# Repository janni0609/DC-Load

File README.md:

# DC Electronic Load

A programmable DC electronic load built on the Raspberry Pi Pico 2 (RP2350). It sinks a user-defined current from a DC source under test and measures voltage, current, power, capacity, and energy in real time on a colour TFT display.

## Hardware

| Component | Part | Interface |
|---|---|---|
| MCU | Raspberry Pi Pico 2 (RP2350) | — |
| Display | ILI9488 TFT 240×320 | SPI (GPIO 16/18/19/17/20) |
| DAC (current setpoint) | DAC80501 16-bit | I2C1 0x48 |
| ADC (V + I measurement) | ADS1115 16-bit | I2C1 0x49 |
| I/O expander (buttons/encoder) | TCAL9539 16-bit | I2C1 0x74 |
| Temperature sensors | 3× MCP9700 | ADC (GPIO 26/27/28) |
| Fans | 2× PWM | GPIO 2, 3 (25 kHz) |
| Beeper | — | GPIO 22 |

I2C1 runs on GPIO 14 (SDA) / GPIO 15 (SCL) at 1 MHz.

### Board design

KiCad design files live in [`hardware/`](hardware/):

- [`hardware/PlugInDC Load/`](hardware/PlugInDC%20Load/) — main plug-in board (MCU, DAC/ADC, pass elements, power supply)
- [`hardware/Front Panel/`](hardware/Front%20Panel/) — front panel board

Each project includes the schematic, PCB layout, a schematic PDF, and a STEP model.

## Specifications

| Parameter | Range |
|---|---|
| Input voltage | 0 – 100 V |
| Set current | 0 – 100 A |
| Under-voltage / CV setpoint (UVP) | 0 – 99.99 V |
| Max power (beeper threshold) | 1000 W |

The DAC output (0–2.5 V) drives the current-control circuit: 2.5 V = 100 A full scale. The ADS1115 uses auto-ranging PGA for both channels, scaling 2.5 V → 100 V (voltage) and 2.5 V → 100 A (current).

## Display Layout

Portrait 240×320, divided into sections:

```
┌──────────────────────────┐
│    DC ELECTRONIC LOAD    │  ← green = load ON, yellow = load OFF
├──────────────────────────┤
│ VOLTAGE          xx.xx V │
├──────────────────────────┤
│ CURRENT         x.xxx A  │
├──────────────────────────┤
│ POWER           xxx.xx W │
├──────────────┬───────────┤
│ CAPACITY x.xxx Ah │ x.xx Wh ENERGY │
├──────────────┬───────────┤
│ SET CURR x.x A │ SET UVP xx.xx V │  ← UVP turns red in CV mode
├──────────────┬───────────┤
│ TEMP  xx.x°C │ HH:MM:SS  │
└──────────────┴───────────┘
```

## Controls

All buttons and the rotary encoder are read via the TCAL9539 I/O expander. Button behaviour is context-sensitive: the main screen, debug screen, and calibration screens each respond differently.

### Main screen

| Input | Function |
|---|---|
| Rotary encoder | Increment/decrement the selected digit of the active setpoint |
| P0.0 (encoder push) | Toggle between editing **SET CURR** and **SET UVP** |
| P0.3 | Move cursor left |
| P0.4 | Move cursor right |
| P0.5 | Switch to debug screen |
| P0.6 | Reset elapsed timer and clear Ah/Wh accumulators |
| P0.7 | Toggle internal / external voltage sense |
| P1.0 | Load ON / OFF (blocked while OTP is active) |

### Debug screen

The debug screen is a navigable menu. P0.3/P0.4 move the selection, the encoder adjusts the highlighted item, and P0.0 (encoder push) activates it.

| Menu item | Function |
|---|---|
| I SENSE | Toggle internal / external current shunt (persisted to EEPROM) |
| VOLT CAL | Enter voltage calibration wizard |
| CURR CAL | Enter current calibration wizard |
| VIEW CAL | Display stored calibration tables |
| OTP TRIP | Set over-temperature protection threshold with encoder (persisted) |
| UVP Kp | Adjust UVP PI proportional gain with encoder (persisted) |
| UVP Ki | Adjust UVP PI integral gain with encoder (persisted) |

### Calibration screen

| Input | Function |
|---|---|
| Rotary encoder | Adjust the entered reference value |
| P0.3 / P0.4 | Move digit cursor left / right |
| P0.0 (encoder push) | Confirm step and advance |
| P0.5 | Cancel and return to debug screen |

## UVP / Constant-Voltage Mode

When **SET UVP** is non-zero and the load is on, a software PI controller monitors the measured voltage. If it drops below the UVP setpoint, the controller reduces the sink current to regulate voltage at that level (constant-voltage / CV mode). The SET UVP field turns red while CV mode is active.

CV mode exits with 0.5 V hysteresis to avoid chattering. The PI gains (Kp, Ki) are tunable from the debug screen and stored in EEPROM.

## Over-Temperature Protection (OTP)

The OTP threshold (default 70 °C, adjustable 30–120 °C) is compared against the highest reading across all three MCP9700 sensors. When the threshold is exceeded:

- The load is turned off immediately.
- Five 500 ms beeps are sounded.
- The load ON button is blocked until the temperature drops 5 °C below the threshold.

## Fan Control

Fan speed is temperature-controlled using the highest reading across all three MCP9700 sensors:

- Off below 30 °C
- Linear ramp from 0–100 % between 30 °C and 50 °C
- Full speed above 50 °C

## Calibration

Both voltage and current channels support piecewise-linear calibration (4 points for voltage, 5 for current). The calibration wizard drives the load to each reference point, reads the raw ADC value, and prompts for the reference meter reading. Calibration data is stored in EEPROM and applied on every measurement via `piecewiseLerp`.

### EEPROM layout

| Address | Content |
|---|---|
| 0 | Current shunt select (0x01 = external) |
| 1 | Current cal valid marker (0xCA) |
| 2 | Voltage cal valid marker (0xCA) |
| 3–42 | Current cal: 5× raw + 5× user (10 floats) |
| 43–74 | Voltage cal: 4× raw + 4× user (8 floats) |
| 75 | OTP valid marker (0xCA) |
| 76–79 | OTP threshold (float) |
| 80 | UVP PI valid marker (0xCA) |
| 81–84 | UVP Kp (float) |
| 85–88 | UVP Ki (float) |

## Building

The project uses [PlatformIO](https://platformio.org/) with the Arduino framework.

```bash
# Build
pio run

# Upload
pio run --target upload

# Serial monitor
pio device monitor --baud 115200
```

Target board: `rpipico2`. Dependencies are fetched automatically (`Bodmer/TFT_eSPI`).

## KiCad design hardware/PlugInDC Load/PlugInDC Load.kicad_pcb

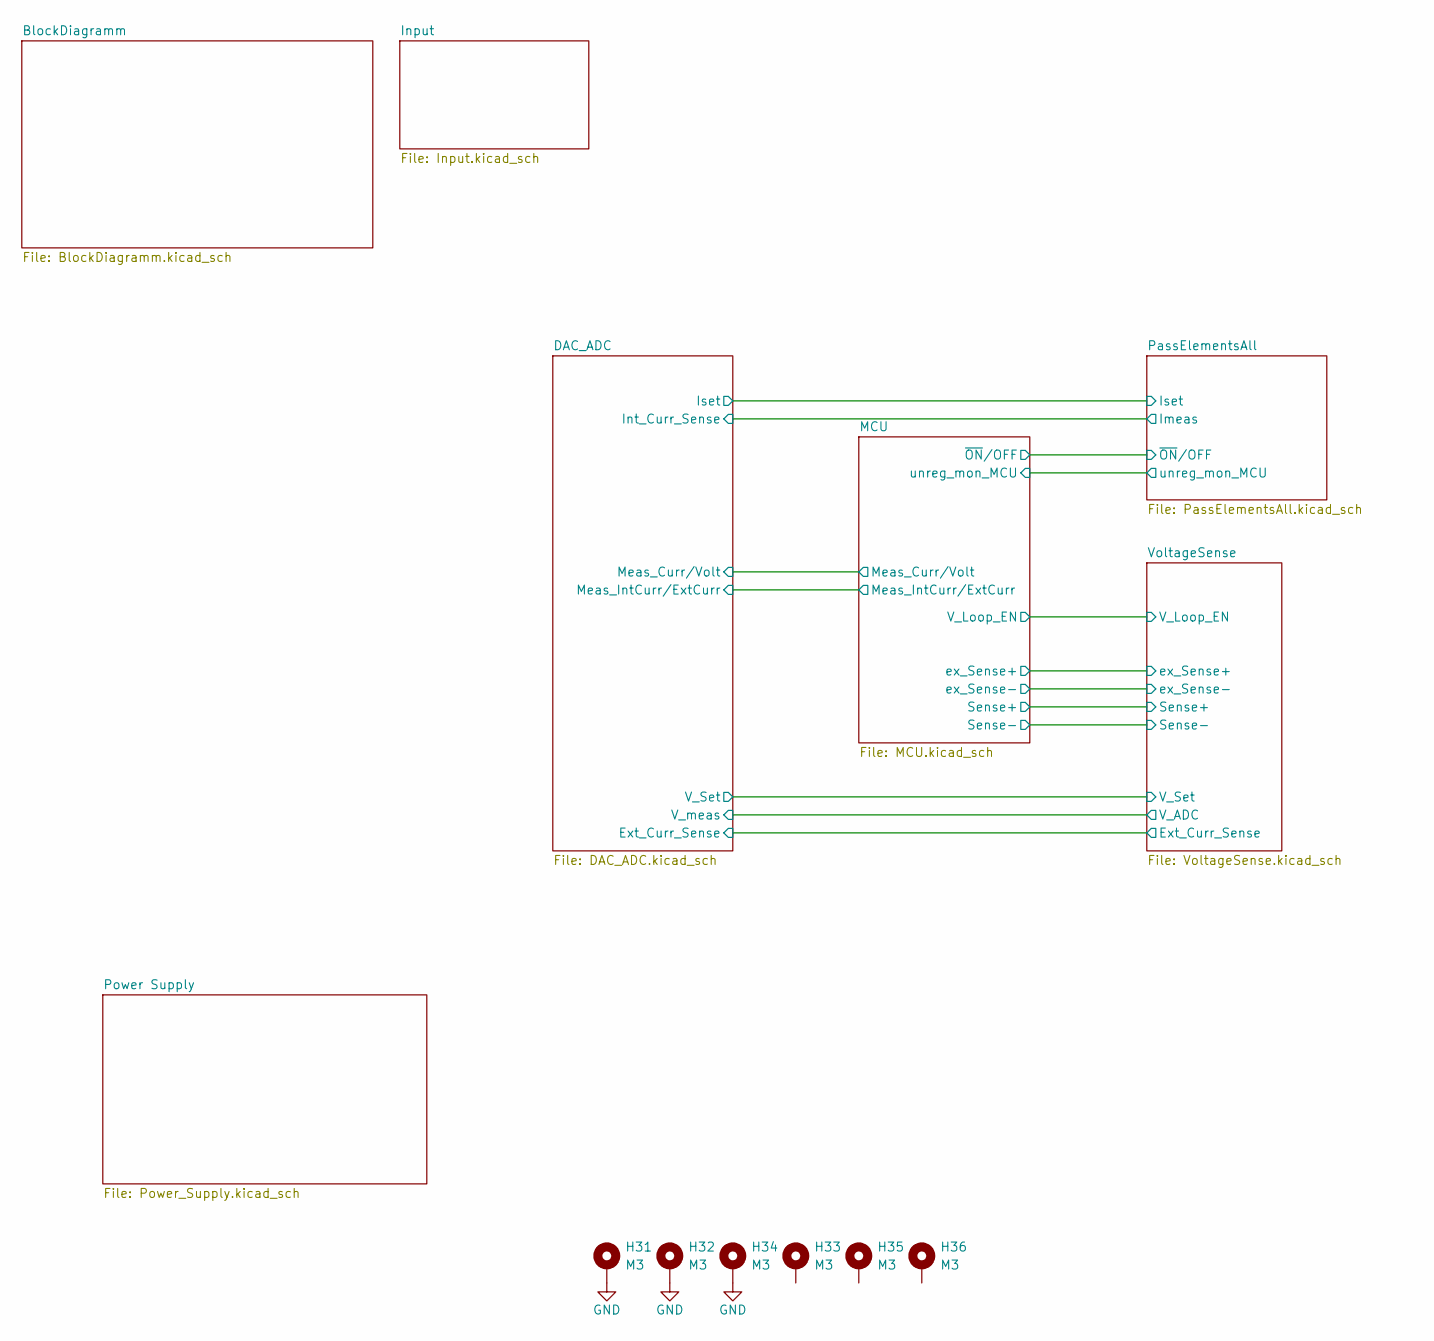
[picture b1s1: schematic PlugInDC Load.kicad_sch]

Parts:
H31, H32, H33, H34, H35, H36: M3; MountingHole_3.2mm_M3_DIN965_Pad

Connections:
GND: H31.1 (1_1), H32.1 (1_1), H34.1 (1_1); also elsewhere on the board

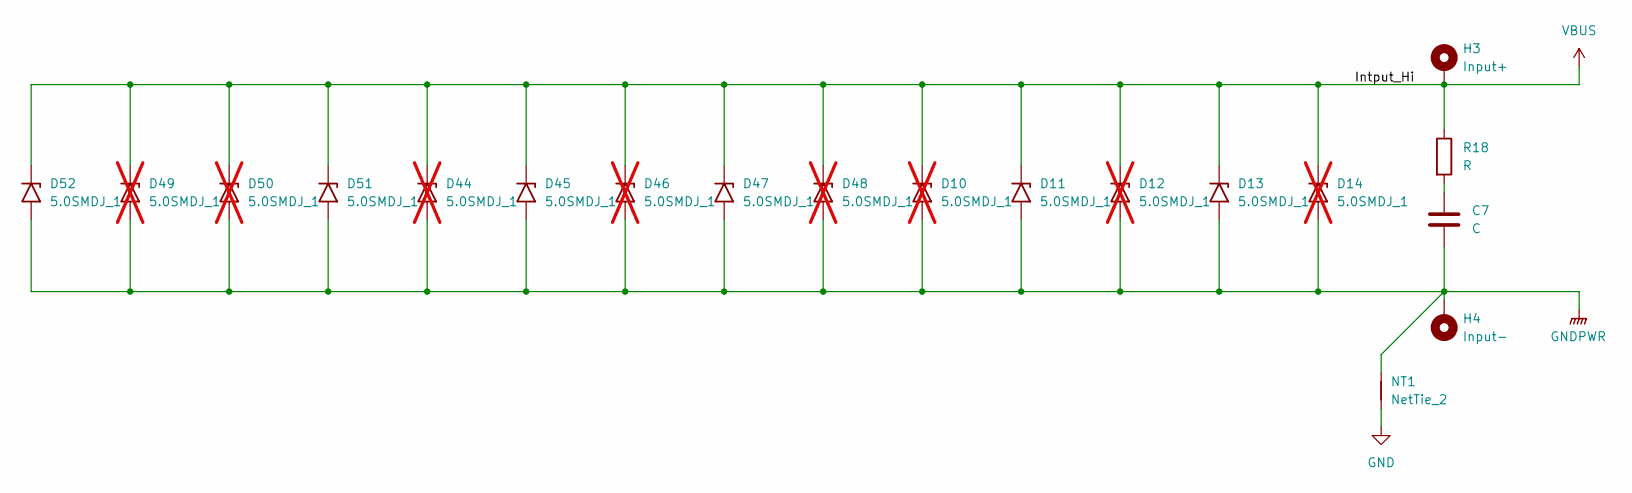
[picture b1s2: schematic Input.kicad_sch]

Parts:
C7: C; C_1206_3216Metric
D10, D12, D14, D44, D46, D48, D49, D50: 5.0SMDJ_1; D_SMC; not fitted
D11, D13, D45, D47, D51, D52: 5.0SMDJ_1; D_SMC
H3: Input+; MountingHole_4.3mm_M4_DIN965_Pad
H4: Input-; MountingHole_4.3mm_M4_DIN965_Pad
NT1: NetTie_2; NetTie-2_SMD_Pad2.0mm
R18: R; R_1206_3216Metric

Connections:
GND: NT1.1; also elsewhere on the board
GNDPWR: C7.2, D10.2 (A2), D11.2 (A2), D12.2 (A2), D13.2 (A2), D14.2 (A2), D44.2 (A2), D45.2 (A2), D46.2 (A2), D47.2 (A2), D48.2 (A2), D49.2 (A2), D50.2 (A2), D51.2 (A2), D52.2 (A2), H4.1 (1_1), NT1.2; also elsewhere on the board
unnamed: C7.1, R18.2
VBUS: D10.1 (A1), D11.1 (A1), D12.1 (A1), D13.1 (A1), D14.1 (A1), D44.1 (A1), D45.1 (A1), D46.1 (A1), D47.1 (A1), D48.1 (A1), D49.1 (A1), D50.1 (A1), D51.1 (A1), D52.1 (A1), H3.1 (1_1), R18.1; also elsewhere on the board

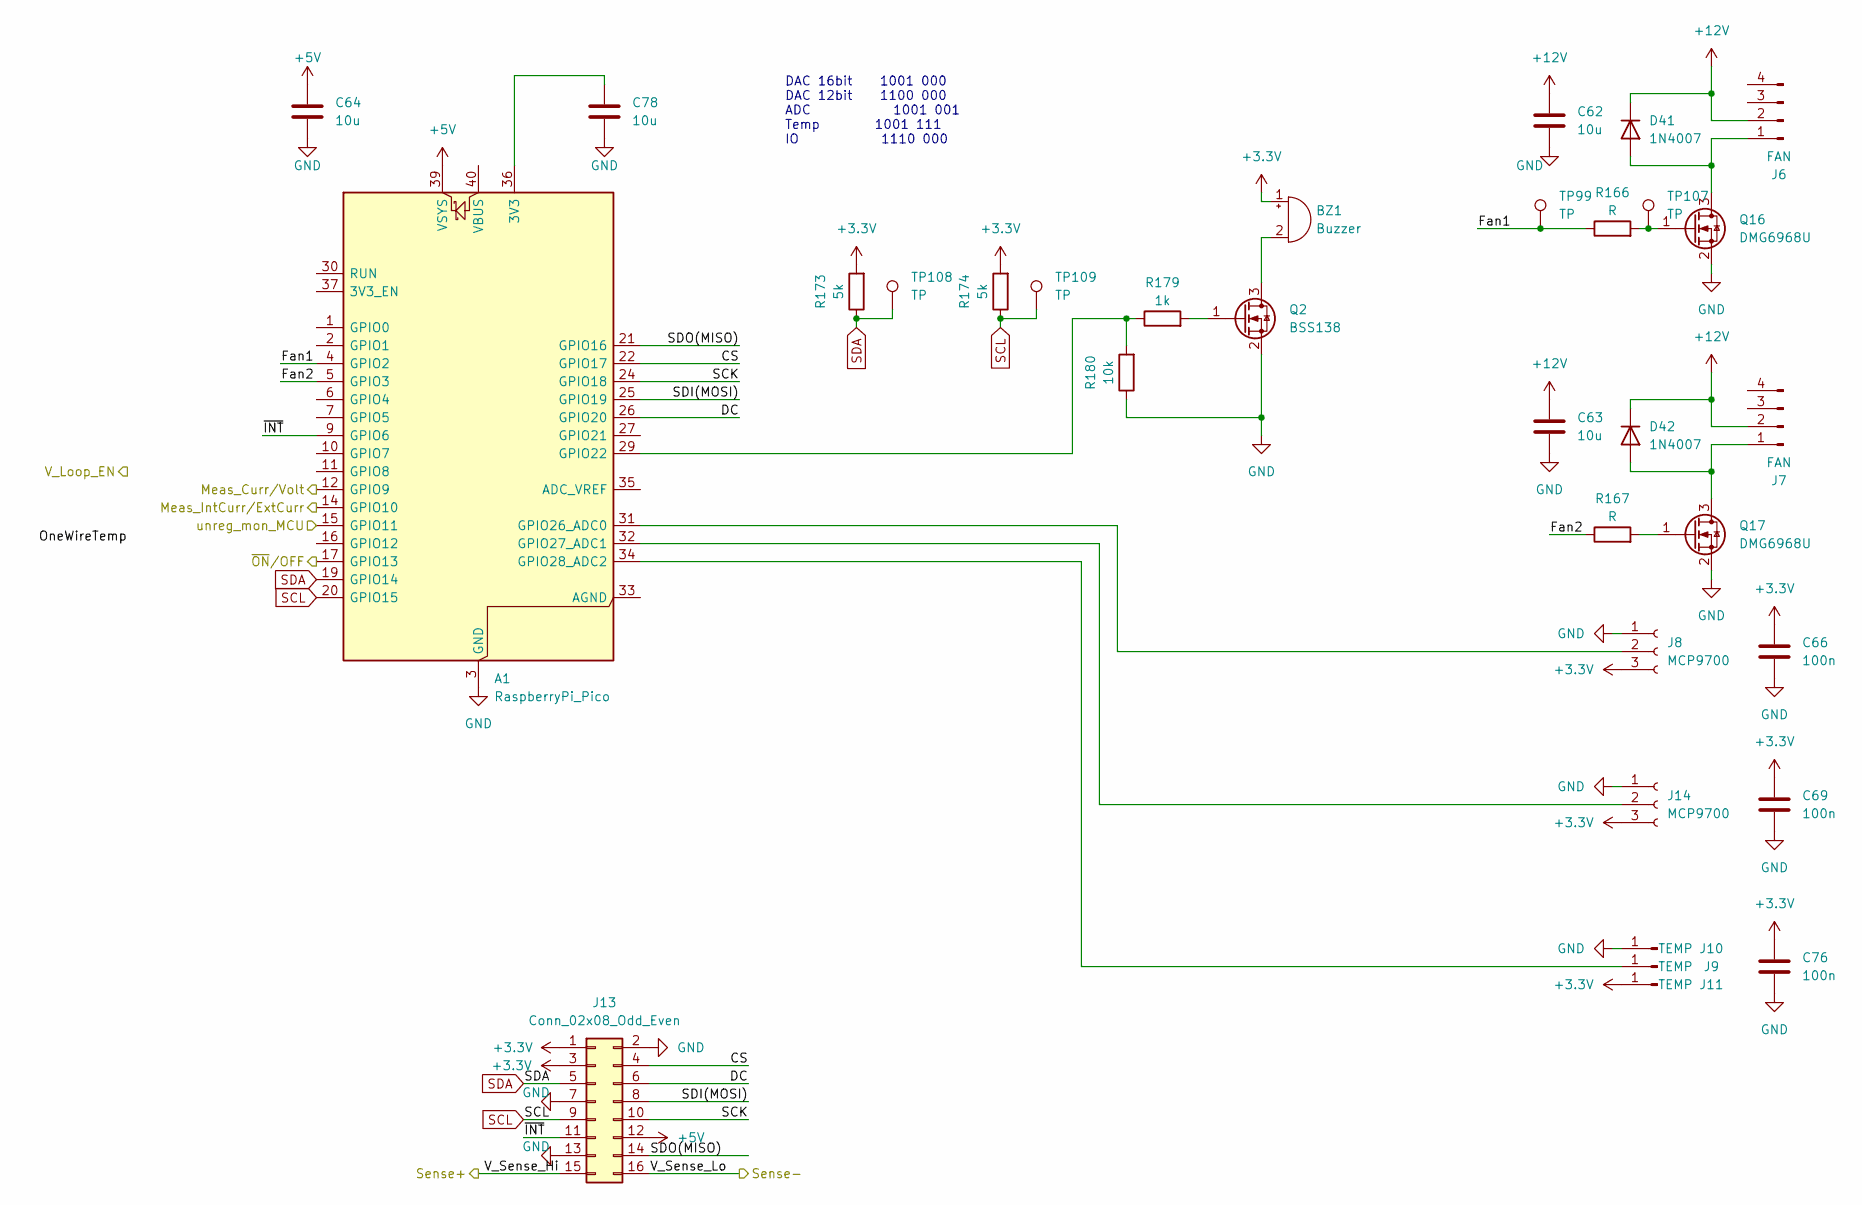
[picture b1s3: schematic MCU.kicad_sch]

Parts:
A1: RaspberryPi_Pico; RaspberryPi_Pico_Common_Unspecified
BZ1: Buzzer; Buzzer_12x9.5RM7.6
C62, C63: 10u; C_1206_3216Metric
C64, C78: 10u; C_0805_2012Metric
C66, C69, C76: 100n; C_0603_1608Metric
D41, D42: 1N4007; D_SOD-123F
J6, J7: FAN; FanPinHeader_1x04_P2.54mm_Vertical
J8, J14: MCP9700; JST_XH_B3B-XH-A_1x03_P2.50mm_Vertical
J9, J10, J11: TEMP; SolderWirePad_1x01_SMD_1.5x3mm
J13: Conn_02x08_Odd_Even; IDC-Header_2x08_P2.54mm_Vertical
Q2: BSS138; SOT-23-3
Q16, Q17: DMG6968U; SOT-23-3
R166, R167: R; R_0603_1608Metric
R173, R174: 5k; R_0603_1608Metric
R179: 1k; R_0603_1608Metric
R180: 10k; R_0603_1608Metric
TP99, TP107, TP108, TP109: TP; TestPoint_Pad_D1.0mm

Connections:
+3.3V: BZ1.1 (+), C66.1, C69.1, C76.1, J8.3, J11.1 (Pin_1_1), J13.1, J13.3, J14.3, R173.2, R174.2; also elsewhere on the board
+5V: A1.39 (VSYS), C64.1, J13.12; also elsewhere on the board
+12V: C62.1, C63.1, D41.1 (K), D42.1 (K), J6.2, J7.2; also elsewhere on the board
/DAC_ADC/Meas_IntCurr/ExtCurr: A1.14 (GPIO10); also elsewhere on the board
/MCU/CS: A1.22 (GPIO17), J13.4
/MCU/DC: A1.26 (GPIO20), J13.6
/MCU/Fan1: A1.4 (GPIO2), R166.1, TP99.1 (1_1)
/MCU/Fan2: A1.5 (GPIO3), R167.1
/MCU/Meas_Curr/Volt: A1.12 (GPIO9)
/MCU/OneWireTemp: A1.16 (GPIO12)
/MCU/SCK: A1.24 (GPIO18), J13.10
/MCU/SDI(MOSI): A1.25 (GPIO19), J13.8
/MCU/SDO(MISO): A1.21 (GPIO16), J13.14
/MCU/V_Loop_EN: A1.11 (GPIO8)
/MCU/V_Sense_Hi: J13.15; also elsewhere on the board
/MCU/V_Sense_Lo: J13.16; also elsewhere on the board
/MCU/unreg_mon_MCU: A1.15 (GPIO11); also elsewhere on the board
/MCU/~INT: A1.9 (GPIO6), J13.11
/MCU/~ON/OFF: A1.17 (GPIO13); also elsewhere on the board
GND: A1.3 (GND), A1.8 (GND), A1.13 (GND), A1.18 (GND), A1.23 (GND), A1.28 (GND), A1.38 (GND), C62.2, C63.2, C64.2, C66.2, C69.2, C76.2, C78.2, J8.1, J10.1 (Pin_1_1), J13.2, J13.7, J13.13, J14.1, Q2.2 (S), Q16.2 (S), Q17.2 (S), R180.1; also elsewhere on the board
unnamed: A1.36 (3V3), C78.1
unnamed: A1.29 (GPIO22), R179.1, R180.2
unnamed: A1.31 (GPIO26_ADC0), J8.2
unnamed: A1.32 (GPIO27_ADC1), J14.2
unnamed: A1.34 (GPIO28_ADC2), J9.1 (Pin_1_1)
unnamed: BZ1.2 (-), Q2.3 (D)
unnamed: D41.2 (A), J6.1, Q16.3 (D)
unnamed: D42.2 (A), J7.1, Q17.3 (D)
unnamed: Q2.1 (G), R179.2
unnamed: Q16.1 (G), R166.2, TP107.1 (1_1)
unnamed: Q17.1 (G), R167.2
SCL: A1.20 (GPIO15), J13.9, R174.1, TP109.1 (1_1); also elsewhere on the board
SDA: A1.19 (GPIO14), J13.5, R173.1, TP108.1 (1_1); also elsewhere on the board

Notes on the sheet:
DAC 16bit 1001 000 DAC 12bit 1100 000 ADC 1001 001 Temp 1001 111 IO 1110 000

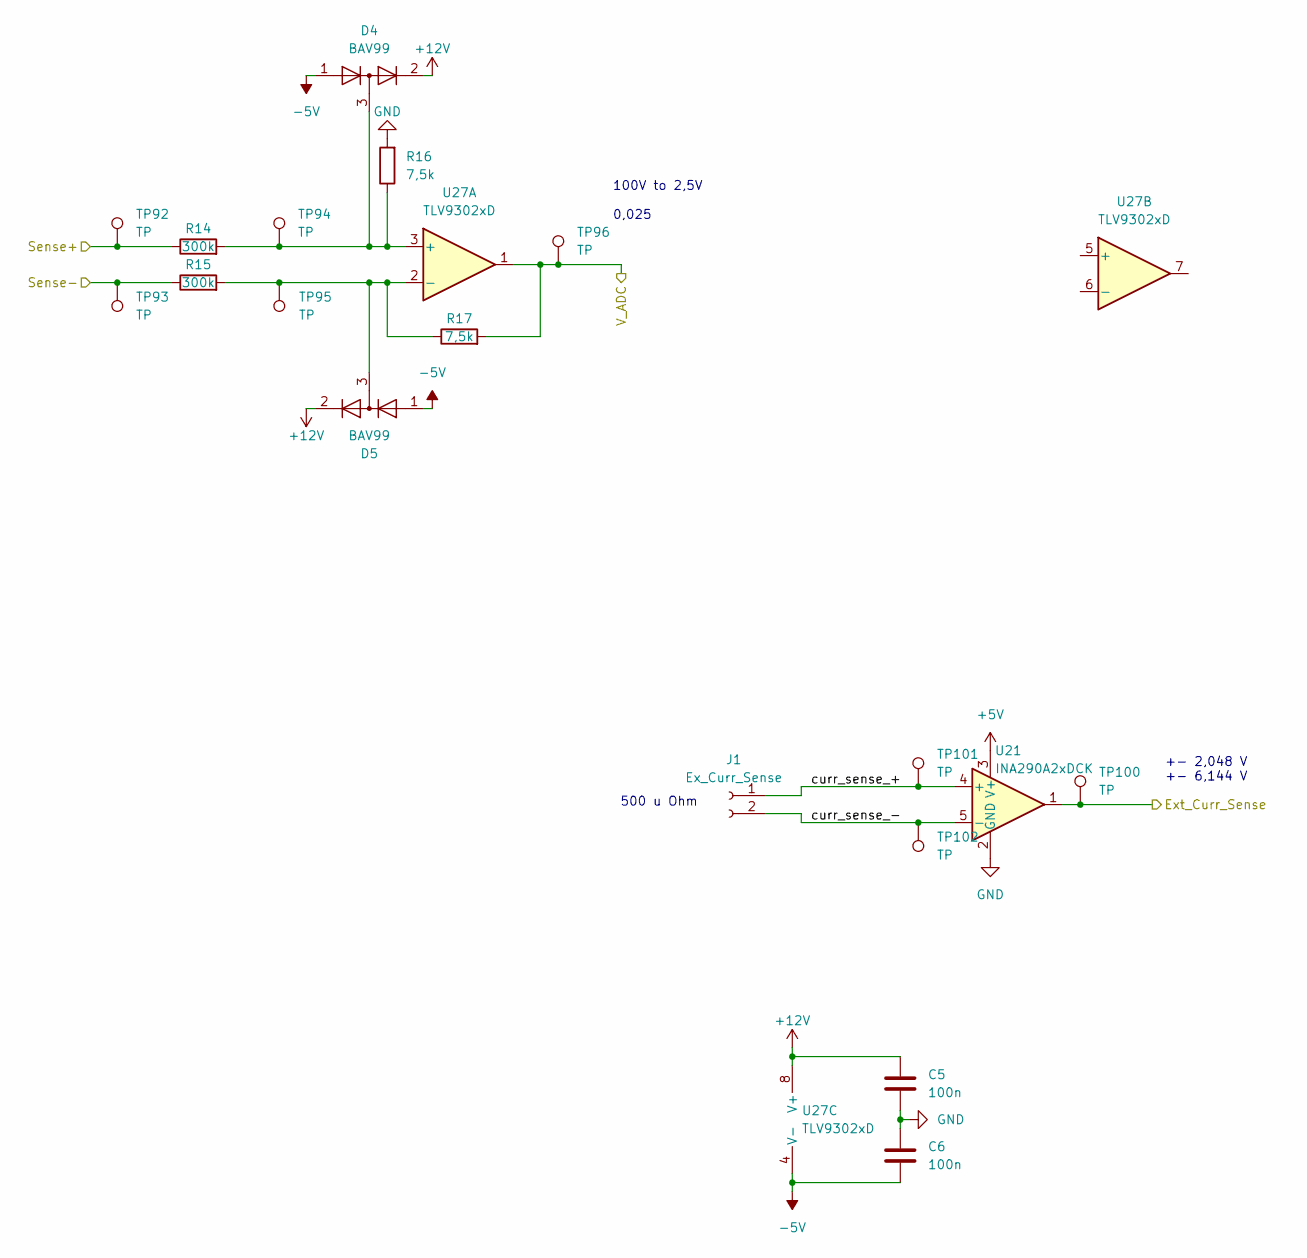
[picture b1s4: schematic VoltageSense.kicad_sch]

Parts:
C5, C6: 100n; C_0603_1608Metric
D4, D5: BAV99; SOT-23-3
J1: Ex_Curr_Sense; JST_XH_B2B-XH-A_1x02_P2.50mm_Vertical
R14, R15: 300k; R_0805_2012Metric
R16, R17: 7,5k; R_0805_2012Metric
TP92, TP93, TP94, TP95, TP96, TP100, TP101, TP102: TP; TestPoint_Pad_D1.0mm
U21: INA290A2xDCK; SOT-353_SC-70-5
U27: TLV9302xD; SOIC-8_3.9x4.9mm_P1.27mm

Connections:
+5V: U21.3 (V+); also elsewhere on the board
+12V: C5.1, D4.2 (A), D5.2 (A), U27.8 (V+); also elsewhere on the board
-5V: C6.2, D4.1 (K), D5.1 (K), U27.4 (V-); also elsewhere on the board
/DAC_ADC/Ext_Curr_Sense: TP100.1 (1_1), U21.1; also elsewhere on the board
/DAC_ADC/V_meas: R17.2, TP96.1 (1_1), U27.1; also elsewhere on the board
/MCU/V_Sense_Hi: R14.1, TP92.1 (1_1); also elsewhere on the board
/MCU/V_Sense_Lo: R15.1, TP93.1 (1_1); also elsewhere on the board
/VoltageSense/curr_sense_+: J1.1, TP101.1 (1_1), U21.4 (+)
/VoltageSense/curr_sense_-: J1.2, TP102.1 (1_1), U21.5 (-)
GND: C5.2, C6.1, R16.2, U21.2 (GND); also elsewhere on the board
unnamed: D4.3 (K), R14.2, R16.1, TP94.1 (1_1), U27.3 (+)
unnamed: D5.3 (K), R15.2, R17.1, TP95.1 (1_1), U27.2 (-)

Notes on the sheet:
500 u Ohm
100V to 2,5V 0,025
+- 2,048 V +- 6,144 V

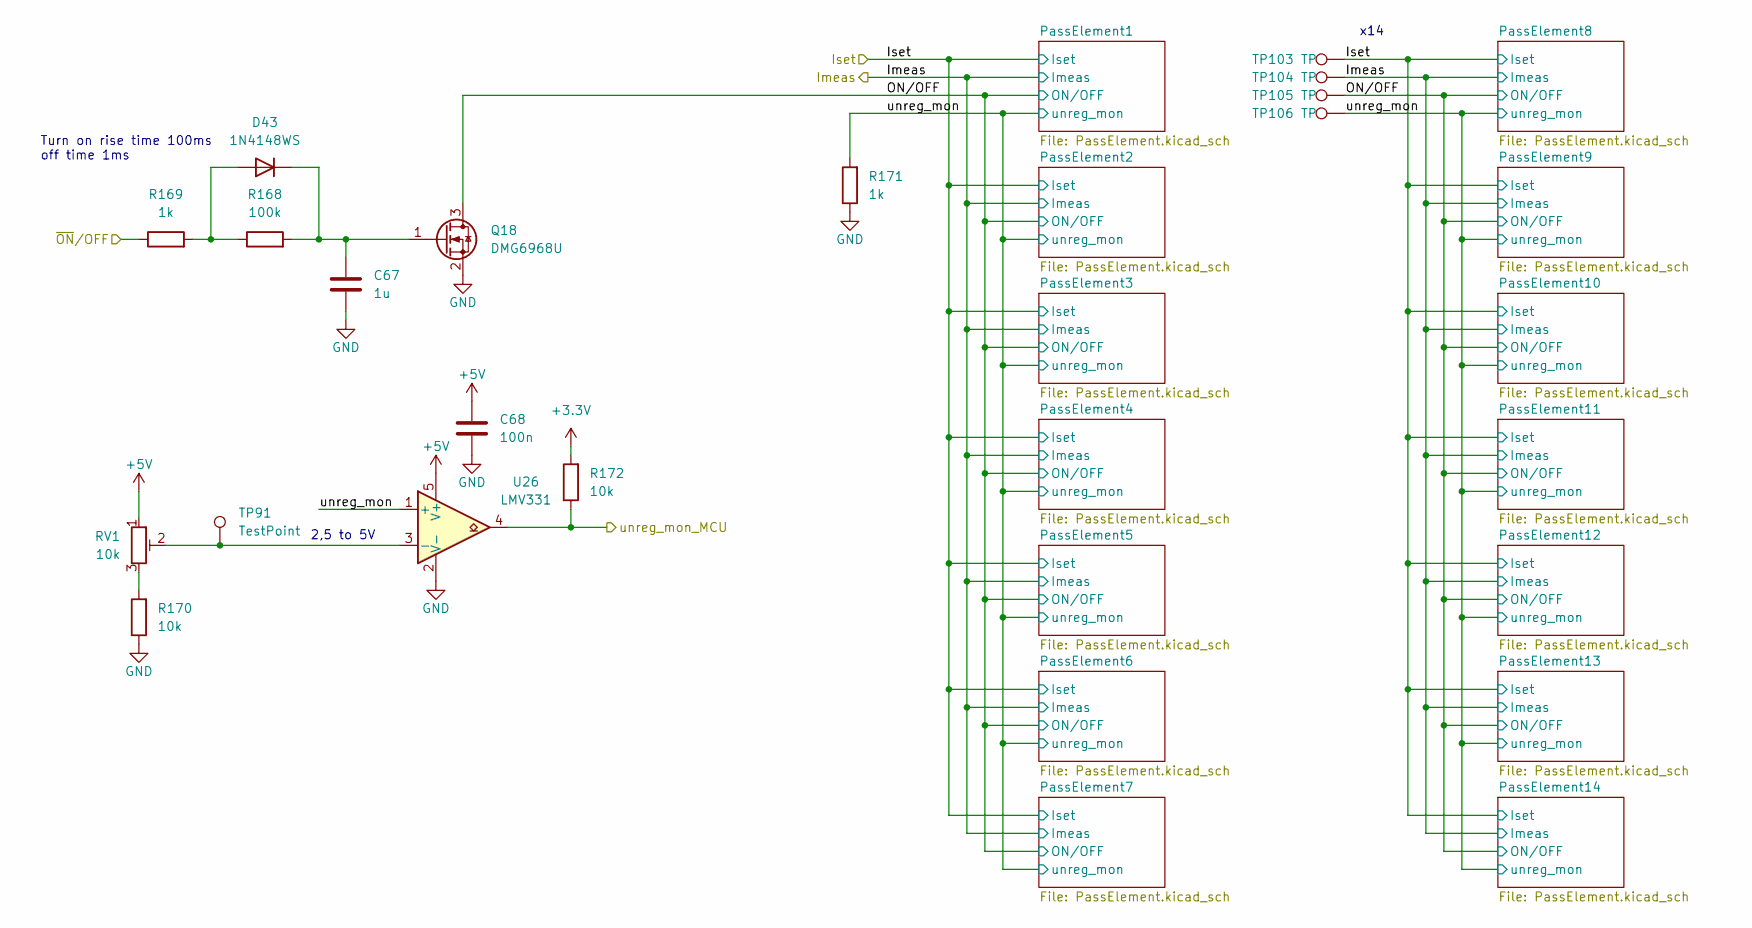
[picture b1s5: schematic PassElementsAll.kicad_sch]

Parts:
C67: 1u; C_0603_1608Metric
C68: 100n; C_0603_1608Metric
D43: 1N4148WS; D_SOD-323
Q18: DMG6968U; SOT-23-3
R168: 100k; R_0603_1608Metric
R169, R171: 1k; R_0603_1608Metric
R170, R172: 10k; R_0603_1608Metric
RV1: 10k; Potentiometer_Bourns_TC33X_Vertical
TP91: TestPoint; TestPoint_Pad_D1.0mm
TP103, TP104, TP105, TP106: TP; TestPoint_Keystone_5005-5009_Compact
U26: LMV331; SOT-23-5

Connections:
+3.3V: R172.2; also elsewhere on the board
+5V: C68.1, RV1.1, U26.5 (V+); also elsewhere on the board
/MCU/unreg_mon_MCU: R172.1, U26.4; also elsewhere on the board
/MCU/~ON/OFF: R169.1; also elsewhere on the board
/PassElementsAll/Imeas: TP104.1 (1_1); also elsewhere on the board
/PassElementsAll/Iset: TP103.1 (1_1); also elsewhere on the board
/PassElementsAll/ON/OFF: Q18.3 (D), TP105.1 (1_1); also elsewhere on the board
/PassElementsAll/unreg_mon: R171.2, TP106.1 (1_1), U26.1 (+); also elsewhere on the board
GND: C67.2, C68.2, Q18.2 (S), R170.1, R171.1, U26.2 (V-); also elsewhere on the board
unnamed: D43.2 (A), R168.1, R169.2
unnamed: C67.1, D43.1 (K), Q18.1 (G), R168.2
unnamed: R170.2, RV1.3
unnamed: RV1.2, TP91.1 (1_1), U26.3 (-)

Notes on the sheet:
x14
Turn on rise time 100ms off time 1ms
2,5 to 5V

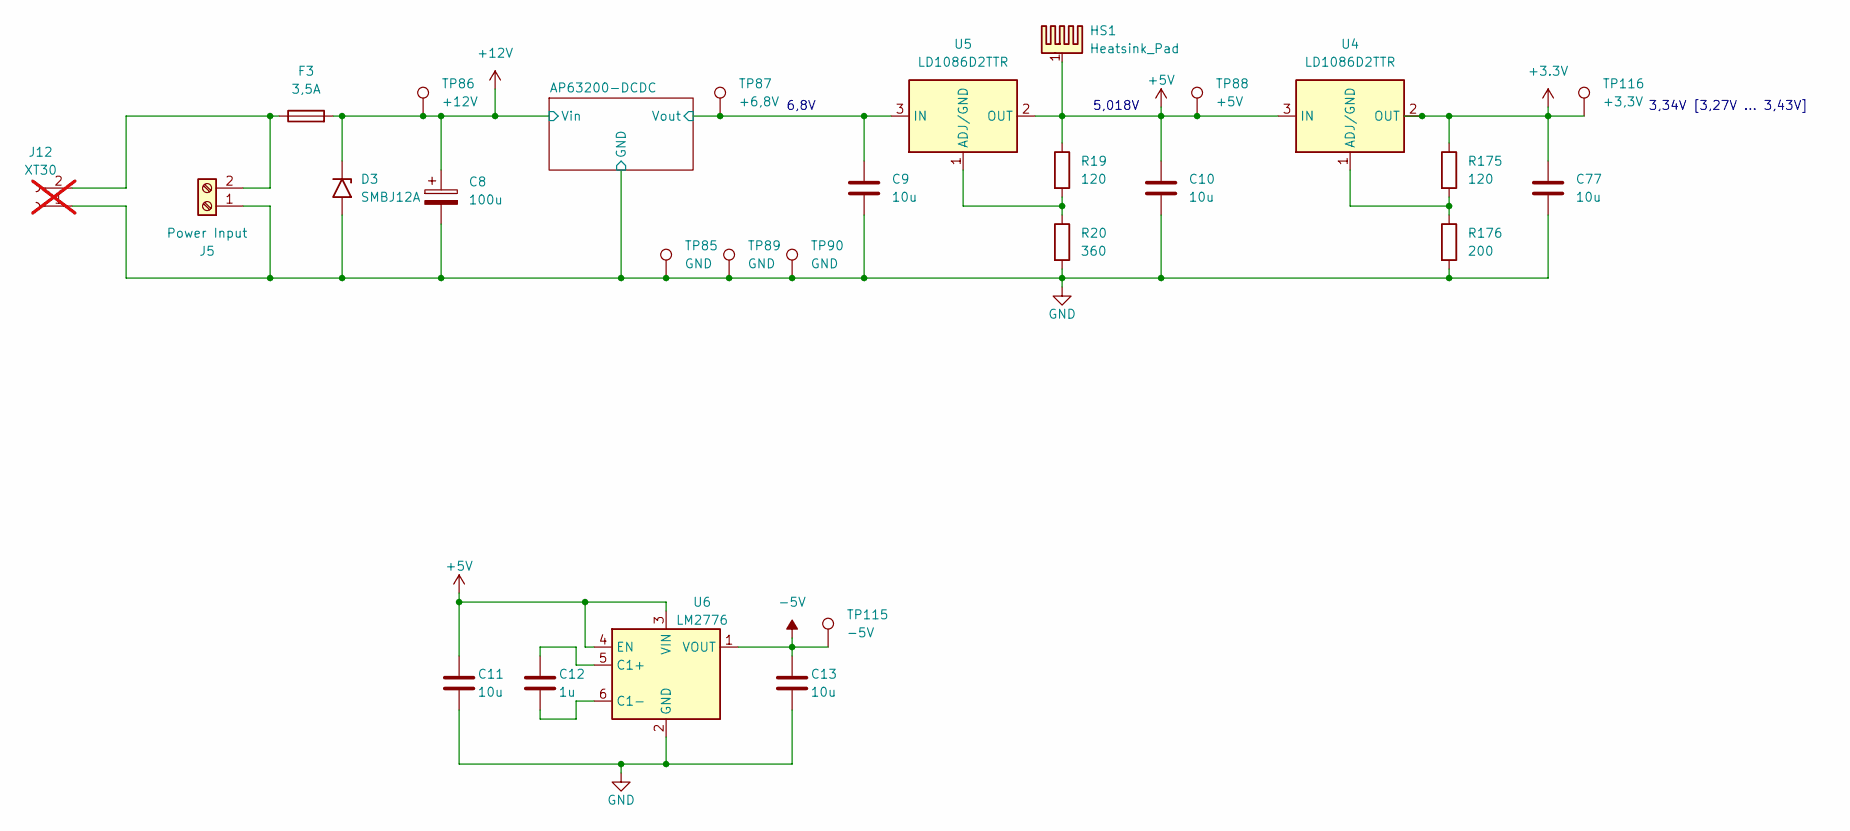
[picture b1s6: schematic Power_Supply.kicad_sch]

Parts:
C8: 100u; CP_Elec_8x10.5
C9, C10, C11, C13, C77: 10u; C_0805_2012Metric
C12: 1u; C_0805_2012Metric
D3: SMBJ12A; D_SMB
F3: 3,5A; Fuse_1206_3216Metric
HS1: Heatsink_Pad; Heatsink_AAVID_573300D00010G_TO-263
J5: Power Input; PhoenixContact_MC_1,5_2-G-3.81_1x02_P3.81mm_Horizontal
J12: XT30; AMASS_XT30PW-M_1x02_P2.50mm_Horizontal; not fitted
R19, R175: 120; R_0603_1608Metric
R20: 360; R_0603_1608Metric
R176: 200; R_0603_1608Metric
TP85, TP89, TP90: GND; TestPoint_Keystone_5005-5009_Compact
TP86: +12V; TestPoint_Keystone_5005-5009_Compact
TP87: +6,8V; TestPoint_Keystone_5005-5009_Compact
TP88: +5V; TestPoint_Keystone_5005-5009_Compact
TP115: -5V; TestPoint_Keystone_5005-5009_Compact
TP116: +3,3V; TestPoint_Keystone_5005-5009_Compact
U4, U5: LD1086D2TTR; TO-263-2
U6: LM2776; SOT-23-6

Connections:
+3.3V: C77.1, R175.1, TP116.1 (1_1), U4.2 (OUT); also elsewhere on the board
+5V: C10.1, C11.1, HS1.1, R19.1, TP88.1 (1_1), U4.3 (IN), U5.2 (OUT), U6.3 (VIN), U6.4 (EN); also elsewhere on the board
+12V: C8.1, D3.1 (A1), F3.2, TP86.1 (1_1); also elsewhere on the board
-5V: C13.1, TP115.1 (1_1), U6.1 (VOUT); also elsewhere on the board
/Power Supply/AP63200-DCDC/Vout: C9.1, TP87.1 (1_1), U5.3 (IN); also elsewhere on the board
GND: C8.2, C9.2, C10.2, C11.2, C13.2, C77.2, D3.2 (A2), J5.1, J12.1, R20.2, R176.2, TP85.1 (1_1), TP89.1 (1_1), TP90.1 (1_1), U6.2 (GND); also elsewhere on the board
unnamed: F3.1, J5.2, J12.2
unnamed: R175.2, R176.1, U4.1 (ADJ/GND)
unnamed: R19.2, R20.1, U5.1 (ADJ/GND)
unnamed: C12.1, U6.5 (C1+)
unnamed: C12.2, U6.6 (C1-)

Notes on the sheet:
6,8V
3,34V [3,27V ... 3,43V]
5,018V

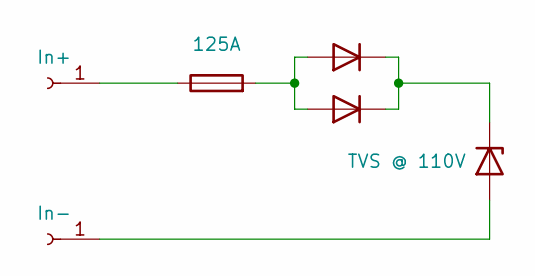
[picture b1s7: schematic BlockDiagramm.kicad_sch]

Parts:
D7, D8: D
D9: TVS @ 110V
F2: 125A
J3: In+
J4: In-

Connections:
unnamed: D7.1 (K), D8.1 (K), D9.1 (K)
unnamed: D7.2 (A), D8.2 (A), F2.2
unnamed: D9.2 (A), J4.1
unnamed: F2.1, J3.1

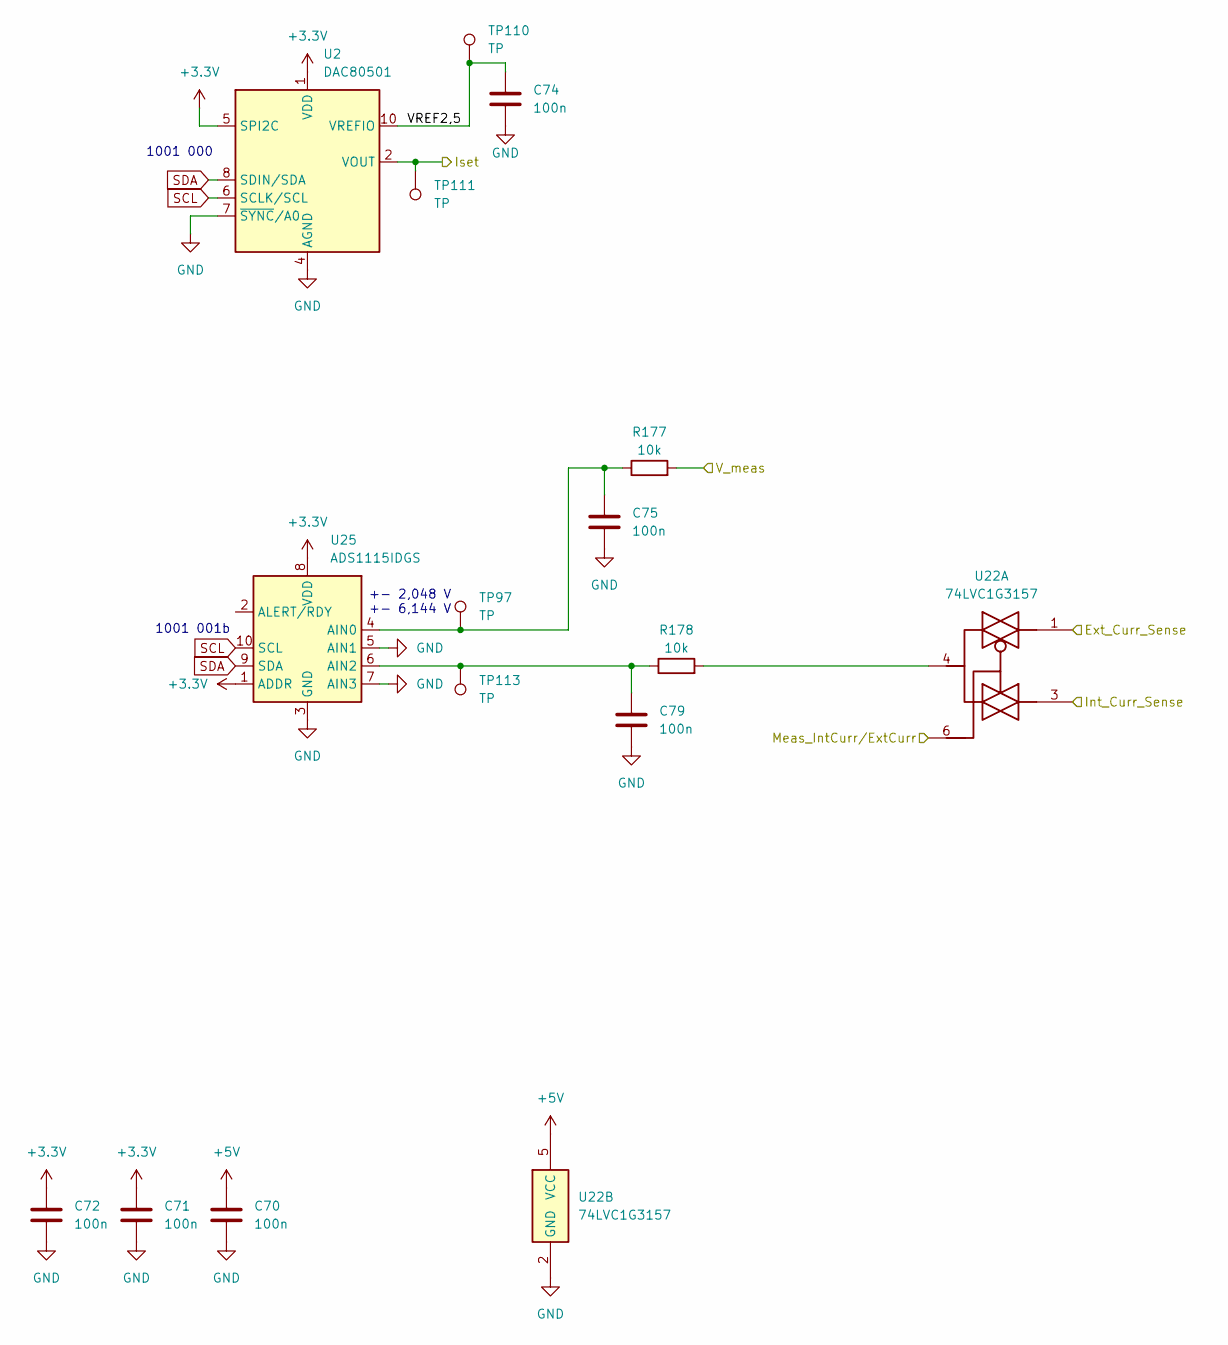
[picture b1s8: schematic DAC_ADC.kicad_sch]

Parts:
C70, C71, C72, C74, C75, C79: 100n; C_0603_1608Metric
R177, R178: 10k; R_0603_1608Metric
TP97, TP110, TP111, TP113: TP; TestPoint_Pad_D1.0mm
U2: DAC80501; VSSOP-10_3x3mm_P0.5mm
U22: 74LVC1G3157; SOT-363_SC-70-6
U25: ADS1115IDGS; TSSOP-10_3x3mm_P0.5mm

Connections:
+3.3V: C71.1, C72.1, U2.1 (VDD), U2.5 (SPI2C), U25.1 (ADDR), U25.8 (VDD); also elsewhere on the board
+5V: C70.1, U22.5 (VCC); also elsewhere on the board
/DAC_ADC/Ext_Curr_Sense: U22.1; also elsewhere on the board
/DAC_ADC/Meas_IntCurr/ExtCurr: U22.6; also elsewhere on the board
/DAC_ADC/VREF2,5: C74.1, TP110.1 (1_1), U2.10 (VREFIO)
/DAC_ADC/V_meas: R177.2; also elsewhere on the board
/PassElementsAll/Imeas: U22.3; also elsewhere on the board
/PassElementsAll/Iset: TP111.1 (1_1), U2.2 (VOUT); also elsewhere on the board
GND: C70.2, C71.2, C72.2, C74.2, C75.2, C79.2, U2.4 (AGND), U2.7 (~SYNC/A0), U22.2 (GND), U25.3 (GND), U25.5 (AIN1), U25.7 (AIN3); also elsewhere on the board
unnamed: R178.2, U22.4
unnamed: C75.1, R177.1, TP97.1 (1_1), U25.4 (AIN0)
unnamed: C79.1, R178.1, TP113.1 (1_1), U25.6 (AIN2)
SCL: U2.6 (SCLK/SCL), U25.10 (SCL); also elsewhere on the board
SDA: U2.8 (SDIN/SDA), U25.9 (SDA); also elsewhere on the board

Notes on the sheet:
1001 001b
1001 000
+- 2,048 V +- 6,144 V
